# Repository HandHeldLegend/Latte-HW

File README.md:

# Latte Project
This is the official Github page for project Latte from Hand Held Legend.

## Software and PCB License
<br />This firmware and PCB model are licensed under a <a rel="license" href="http://creativecommons.org/licenses/by-nc-sa/3.0/">Creative Commons Attribution-NonCommercial-ShareAlike 3.0 Unported License</a>.

## 3D Models License

<br />The 3D shell, buttons, and other associated models are licensed under a <a rel="license" href="http://creativecommons.org/licenses/by/4.0/">Creative Commons Attribution 4.0 International License</a>.

## Attributions

Resources Cross-Referenced for shell shape:
- 3D Scans by Wesk

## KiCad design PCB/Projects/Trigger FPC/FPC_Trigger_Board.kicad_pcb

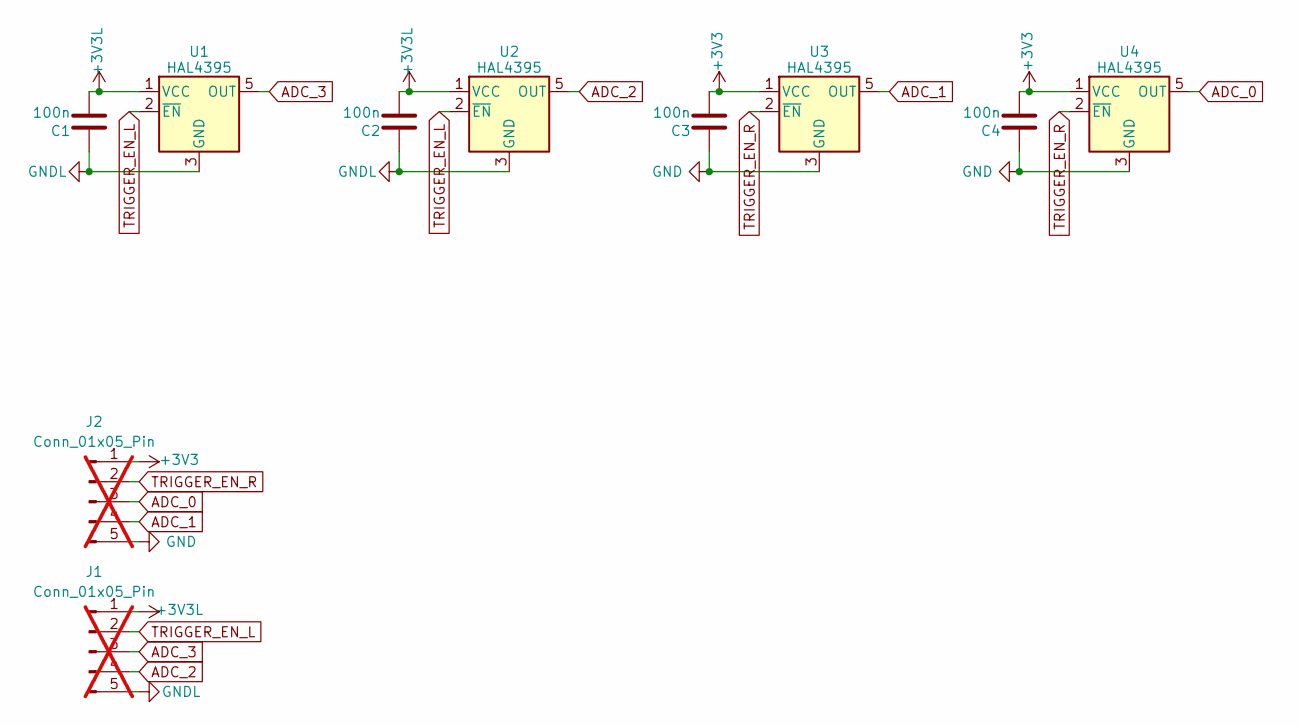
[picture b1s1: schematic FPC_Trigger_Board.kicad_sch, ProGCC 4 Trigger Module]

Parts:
C1, C2, C3, C4: 100n; C_0201_0603Metric; MPN GRM033R61A104KE15D; LCSC C76934
J1, J2: Conn_01x05_Pin; 505110-0592 Ribbon; not fitted
U1, U2, U3, U4: HAL4395; SOT-23-5L; MPN HAL4395SO5; LCSC C49165022

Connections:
+3V3: C3.2, C4.2, J2.1, U3.1 (VCC), U4.1 (VCC)
+3V3L: C1.2, C2.2, J1.1, U1.1 (VCC), U2.1 (VCC)
ADC_0: J2.3, U4.5 (OUT)
ADC_1: J2.4, U3.5 (OUT)
ADC_2: J1.4, U2.5 (OUT)
ADC_3: J1.3, U1.5 (OUT)
GND: C3.1, C4.1, J2.5, U3.3 (GND), U4.3 (GND)
GNDL: C1.1, C2.1, J1.5, U1.3 (GND), U2.3 (GND)
TRIGGER_EN_L: J1.2, U1.2 (~EN), U2.2 (~EN)
TRIGGER_EN_R: J2.2, U3.2 (~EN), U4.2 (~EN)

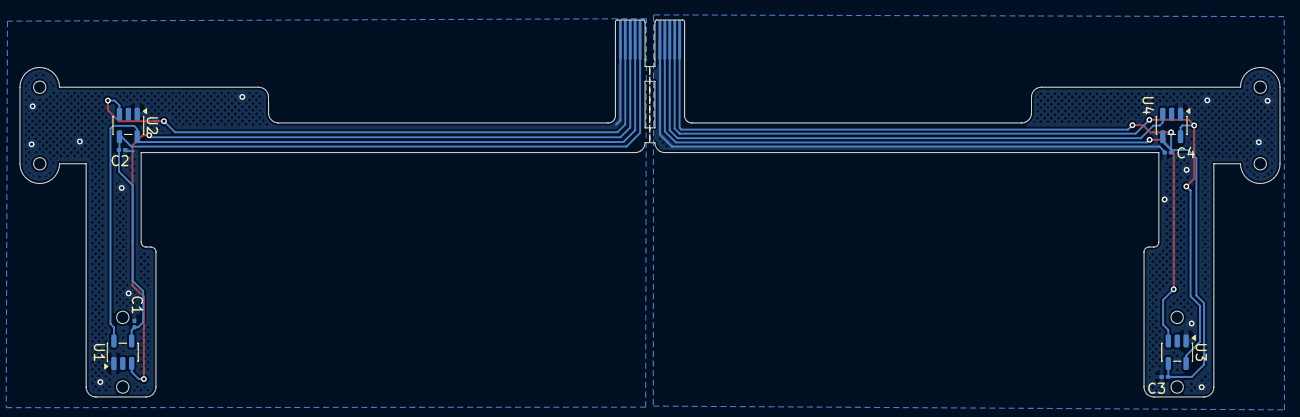
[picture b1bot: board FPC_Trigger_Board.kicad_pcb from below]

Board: 2 copper layers, 127.6 x 38.2 mm, 10 parts (8 on the bottom side), 10 nets.

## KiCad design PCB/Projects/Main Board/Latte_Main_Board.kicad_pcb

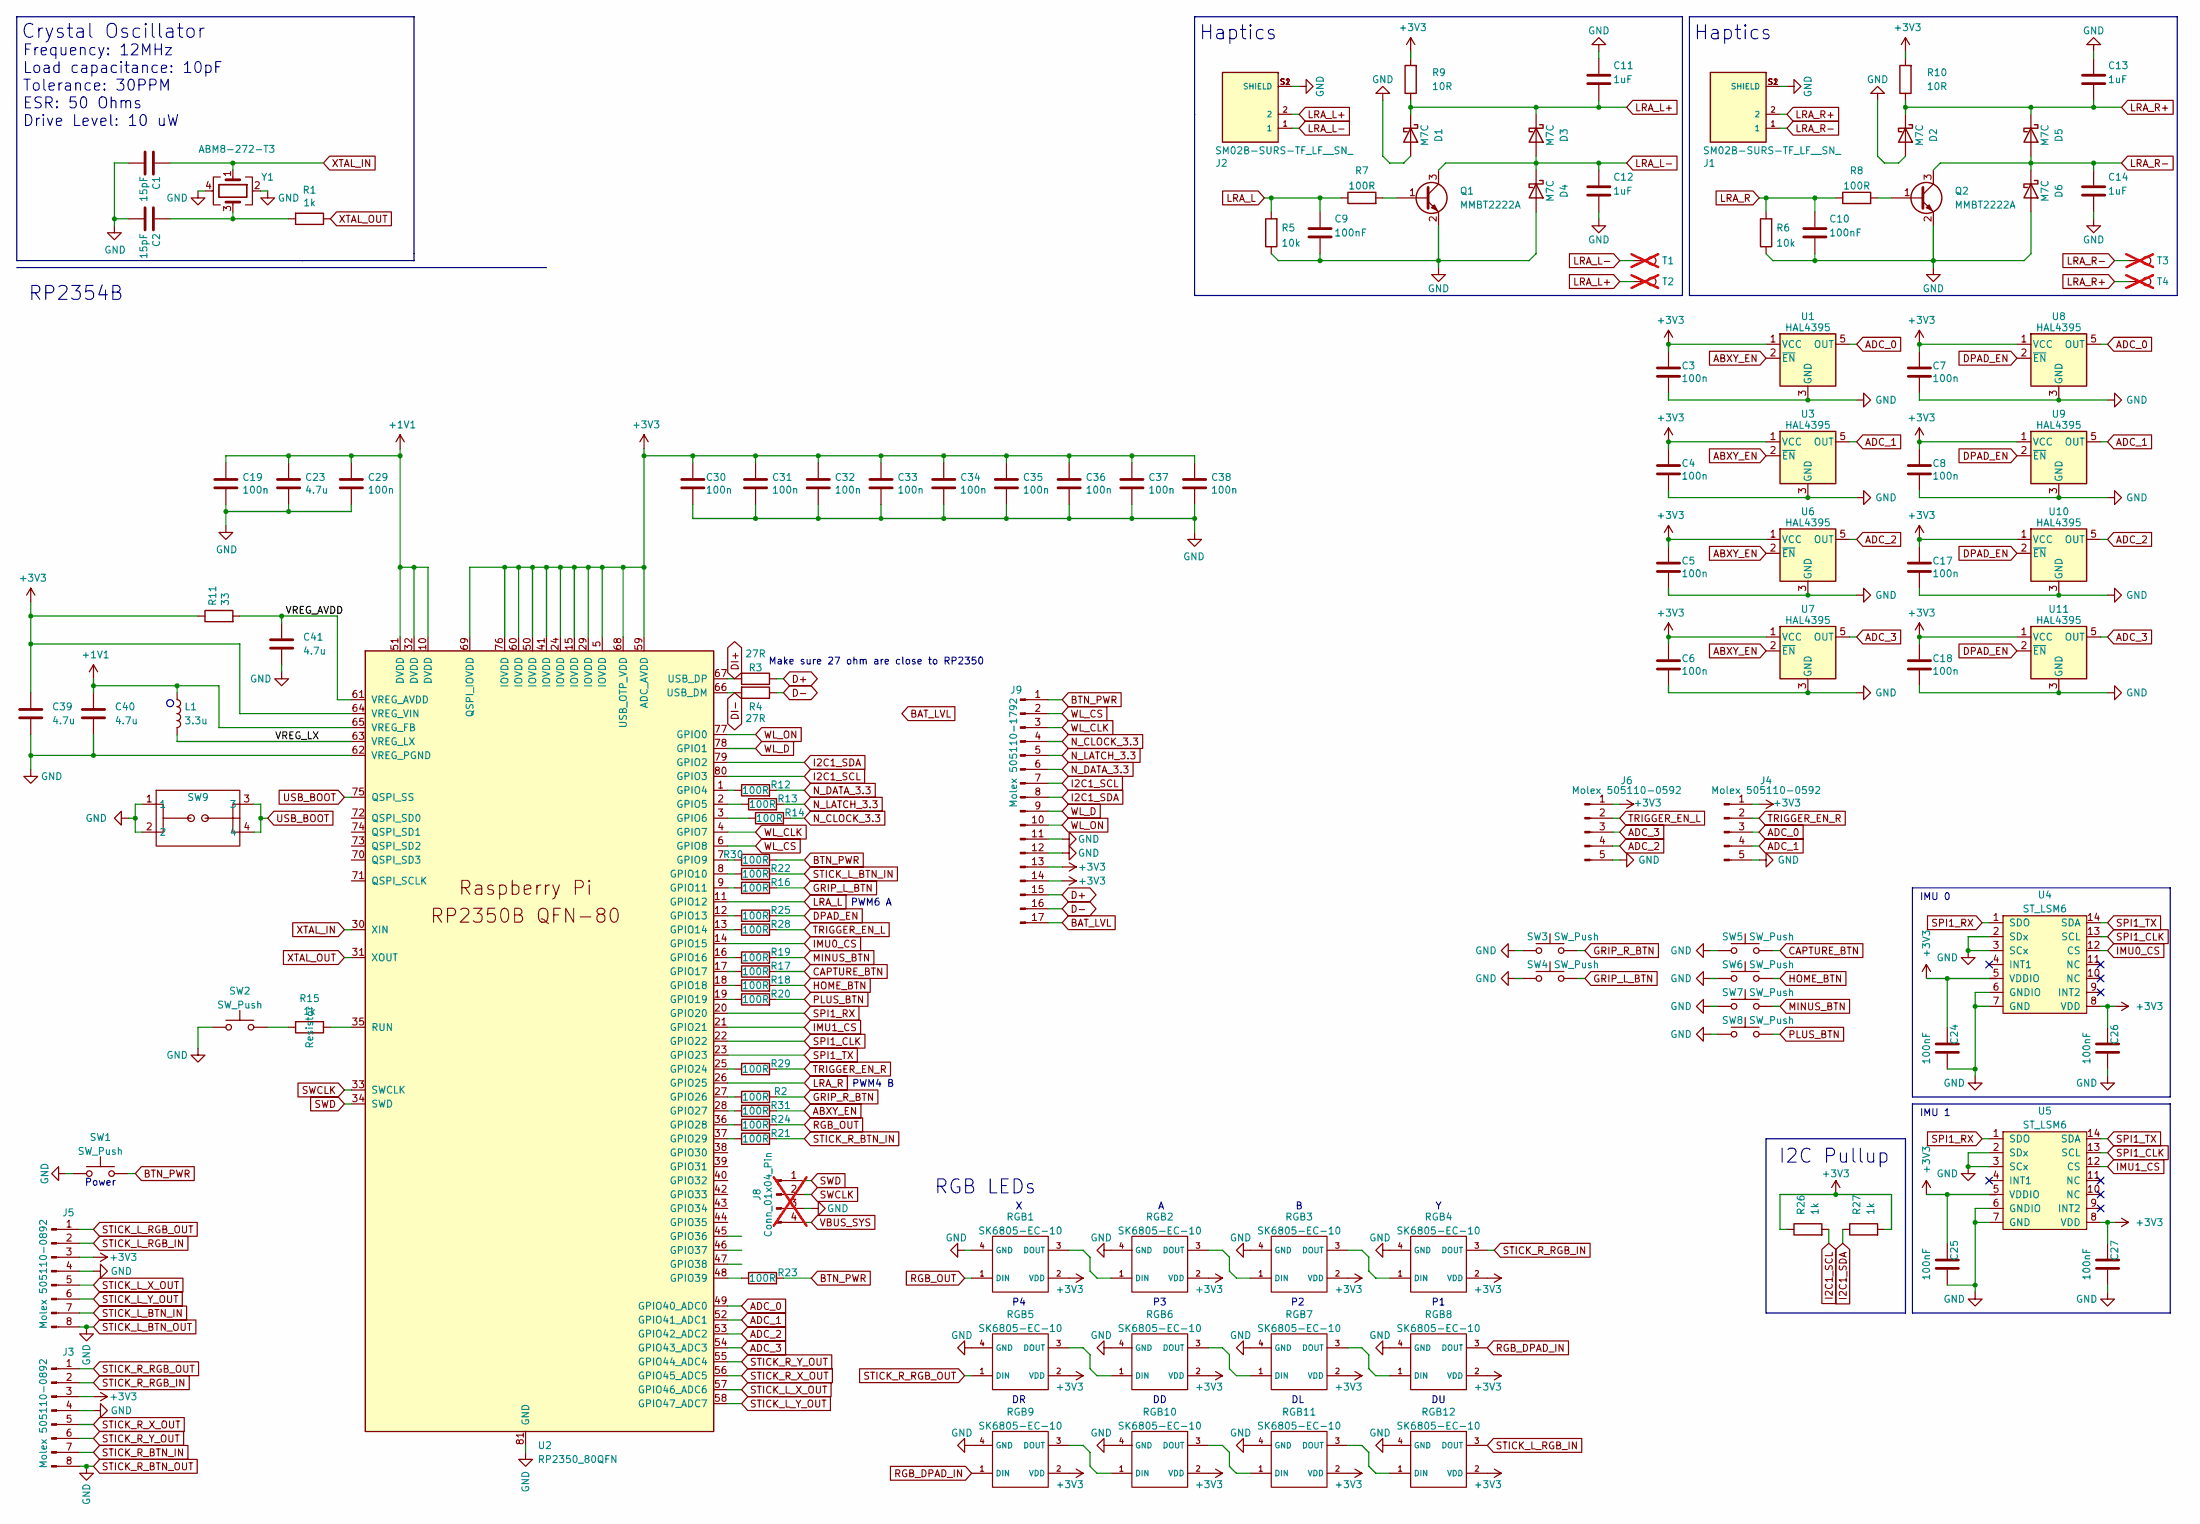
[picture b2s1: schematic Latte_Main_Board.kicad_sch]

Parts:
C1, C2: 15pF; C_0402_1005Metric; MPN CC0402FRNPO9BN150; LCSC C326803
C3, C4, C5, C6, C7, C8, C17, C18, C19, C29, C30, C31, C32, C33, C34, C35, C36, C37, C38: 100n; C_0201_0603Metric; MPN GRM033R61A104KE15D; LCSC C76934
C9, C10, C24, C25, C26, C27: 100nF; C_0201_0603Metric; MPN CL03A104KQ3NNNC; LCSC C160831
C11, C12, C13, C14: 1uF; C_0201_0603Metric; MPN GRM033R60J105KEA2D; LCSC C76929
C23, C39, C40, C41: 4.7u; C_0402_1005Metric; MPN CL05A475KP5NRNC; LCSC C368809
D1, D2, D3, D4, D5, D6: M7C; D_SOD-523; MPN B5819WT; LCSC C5364321
J1, J2: SM02B-SURS-TF_LF__SN_; JST_SM02B-SURS-TF_LF__SN_; PARTREV N/A; LCSC C566239
J3, J5: Molex 505110-0892; 5051100892; MPN 505110-0892; LCSC C5902847
J4, J6: Molex 505110-0592; 5051100592; MPN 505110-0592; LCSC C3168457
J8: Conn_01x04_Pin; PinHeader_1x04_P2.00mm_Vertical; not fitted
J9: Molex 505110-1792; 5051101792; MPN 505110-1792; LCSC C6819458
L1: 3.3u; L_pol_2016; MPN AOTA-B201610S3R3-101-T; LCSC C42411119
Q1, Q2: MMBT2222A; SOT-23; MPN MMBT2222A; LCSC C916372
R1, R15, R26, R27: 1k; R_0201_0603Metric; MPN RC0201FR-071KL; LCSC C138165
R2, R7, R8, R12, R13, R14, R16, R17, R18, R19, R20, R21, R22, R23, R24, R25, R28, R29, R30, R31: 100R; R_0201_0603Metric; MPN RC0201FR-07100RL; LCSC C77623
R3, R4: 27R; R_0201_0603Metric; MPN RC0201FR-0727RL; LCSC C273268
R5, R6: 10k; R_0201_0603Metric; MPN RC0201FR-0710KL; LCSC C106225
R9, R10: 10R; R_0201_0603Metric; MPN RC0201FR-0710RL; LCSC C106226
R11: 33; R_0201_0603Metric; MPN RC0201FR-0733RL; LCSC C295794
RGB1, RGB2, RGB3, RGB4, RGB5, RGB6, RGB7, RGB8, RGB9, RGB10, RGB11, RGB12: SK6805-EC-10; MPN SK6805-EC-10; LCSC C22394946
SW1, SW2, SW3, SW4, SW5, SW6, SW7, SW8: SW_Push; KSC-TE; MPN KSC201J LFS; LCSC C221725
SW9: 1TS026A-1000-0550; MPN 1TS026A-1000-0550; LCSC C913778
T1, T2, T3, T4: PinHeader_1x01_P1.00mm_Vertical; not fitted
U1, U3, U6, U7, U8, U9, U10, U11: HAL4395; SOT-23-5L; MPN HAL4395SO5; LCSC C49165022
U2: RP2350_80QFN; RP2350-QFN-80-1EP_10x10_P0.4mm_EP3.4x3.4mm_ThermalVias; MPN RP2354B; LCSC C39843328
U4, U5: ST_LSM6; LGA14; MPN LSM6DSLTR; LCSC C126672
Y1: ABM8-272-T3; Crystal_SMD_3225-4Pin_3.2x2.5mm; MPN ABM8-272-T3; LCSC C20625731

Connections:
+1V1: C19.1, C23.1, C29.1, C40.1, L1.1, U2.10 (DVDD), U2.32 (DVDD), U2.51 (DVDD), U2.65 (VREG_FB)
+3V3: C3.1, C4.1, C5.1, C6.1, C7.1, C8.1, C17.1, C18.1, C24.2, C25.2, C26.2, C27.2, C30.1, C31.1, C32.1, C33.1, C34.1, C35.1, C36.1, C37.1, C38.1, C39.1, J3.3, J4.1, J5.3, J6.1, J9.13, J9.14, R9.2, R10.2, R11.1, R26.1, R27.2, RGB1.2 (VDD), RGB2.2 (VDD), RGB3.2 (VDD), RGB4.2 (VDD), RGB5.2 (VDD), RGB6.2 (VDD), RGB7.2 (VDD), RGB8.2 (VDD), RGB9.2 (VDD), RGB10.2 (VDD), RGB11.2 (VDD), RGB12.2 (VDD), U1.1 (VCC), U2.5 (IOVDD), U2.15 (IOVDD), U2.24 (IOVDD), U2.29 (IOVDD), U2.41 (IOVDD), U2.50 (IOVDD), U2.59 (ADC_AVDD), U2.60 (IOVDD), U2.64 (VREG_VIN), U2.68 (USB_OTP_VDD), U2.69 (QSPI_IOVDD), U2.76 (IOVDD), U3.1 (VCC), U4.5 (VDDIO), U4.8 (VDD), U5.5 (VDDIO), U5.8 (VDD), U6.1 (VCC), U7.1 (VCC), U8.1 (VCC), U9.1 (VCC), U10.1 (VCC), U11.1 (VCC)
/VREG_AVDD: C41.1, R11.2, U2.61 (VREG_AVDD)
/VREG_LX: L1.2, U2.63 (VREG_LX)
ABXY_EN: R31.2, U1.2 (~EN), U3.2 (~EN), U6.2 (~EN), U7.2 (~EN)
ADC_0: J4.3, U1.5 (OUT), U2.49 (GPIO40_ADC0), U8.5 (OUT)
ADC_1: J4.4, U2.52 (GPIO41_ADC1), U3.5 (OUT), U9.5 (OUT)
ADC_2: J6.4, U2.53 (GPIO42_ADC2), U6.5 (OUT), U10.5 (OUT)
ADC_3: J6.3, U2.54 (GPIO43_ADC3), U7.5 (OUT), U11.5 (OUT)
BAT_LVL: J9.17
BTN_PWR: J9.1, R23.2, R30.2, SW1.2
CAPTURE_BTN: R17.2, SW5.2
D+: J9.15, R3.1
D-: J9.16, R4.1
DI+: R3.2, U2.67 (USB_DP)
DI-: R4.2, U2.66 (USB_DM)
DPAD_EN: R25.2, U8.2 (~EN), U9.2 (~EN), U10.2 (~EN), U11.2 (~EN)
GRIP_L_BTN: R16.2, SW4.2
GRIP_R_BTN: R2.2, SW3.2
HOME_BTN: R18.2, SW6.2
I2C1_SCL: J9.7, R26.2, U2.80 (GPIO3)
I2C1_SDA: J9.8, R27.1, U2.79 (GPIO2)
IMU0_CS: U2.14 (GPIO15), U4.12 (CS)
IMU1_CS: U2.21 (GPIO21), U5.12 (CS)
LRA_L: C9.1, R5.2, R7.1, U2.11 (GPIO12)
LRA_L+: C11.2, D1.1 (K), D3.1 (K), J2.2, R9.1, T2.1
LRA_L-: C12.1, D3.2 (A), D4.1 (K), J2.1, Q1.3 (C), T1.1
LRA_R: C10.1, R6.2, R8.1, U2.26 (GPIO25)
LRA_R+: C13.2, D2.1 (K), D5.1 (K), J1.2, R10.1, T4.1
LRA_R-: C14.1, D5.2 (A), D6.1 (K), J1.1, Q2.3 (C), T3.1
MINUS_BTN: R19.2, SW7.2
N_CLOCK_3.3: J9.4, R14.2
N_DATA_3.3: J9.6, R12.2
N_LATCH_3.3: J9.5, R13.2
unnamed: C2.1, R1.2, Y1.3
unnamed: Q1.1 (B), R7.2
unnamed: Q2.1 (B), R8.2
unnamed: R15.2, SW2.2
unnamed: RGB1.3 (DOUT), RGB2.1 (DIN)
unnamed: RGB2.3 (DOUT), RGB3.1 (DIN)
unnamed: RGB3.3 (DOUT), RGB4.1 (DIN)
unnamed: RGB5.3 (DOUT), RGB6.1 (DIN)
unnamed: RGB6.3 (DOUT), RGB7.1 (DIN)
unnamed: RGB7.3 (DOUT), RGB8.1 (DIN)
unnamed: RGB9.3 (DOUT), RGB10.1 (DIN)
unnamed: RGB10.3 (DOUT), RGB11.1 (DIN)
unnamed: RGB11.3 (DOUT), RGB12.1 (DIN)
unnamed: R12.1, U2.1 (GPIO4)
unnamed: R13.1, U2.2 (GPIO5)
unnamed: R14.1, U2.3 (GPIO6)
unnamed: R30.1, U2.7 (GPIO9)
unnamed: R22.1, U2.8 (GPIO10)
unnamed: R16.1, U2.9 (GPIO11)
unnamed: R25.1, U2.12 (GPIO13)
unnamed: R28.1, U2.13 (GPIO14)
unnamed: R19.1, U2.16 (GPIO16)
unnamed: R17.1, U2.17 (GPIO17)
unnamed: R18.1, U2.18 (GPIO18)
unnamed: R20.1, U2.19 (GPIO19)
unnamed: R29.1, U2.25 (GPIO24)
unnamed: R2.1, U2.27 (GPIO26)
unnamed: R31.1, U2.28 (GPIO27)
unnamed: R24.1, U2.36 (GPIO28)
unnamed: R21.1, U2.37 (GPIO29)
unnamed: R23.1, U2.48 (GPIO39)
unnamed: R15.1, U2.35 (RUN)
PLUS_BTN: R20.2, SW8.2
RGB_DPAD_IN: RGB8.3 (DOUT), RGB9.1 (DIN)
RGB_OUT: R24.2, RGB1.1 (DIN)
SPI1_CLK: U2.22 (GPIO22), U4.13 (SCL), U5.13 (SCL)
SPI1_RX: U2.20 (GPIO20), U4.1 (SDO), U5.1 (SDO)
SPI1_TX: U2.23 (GPIO23), U4.14 (SDA), U5.14 (SDA)
STICK_L_BTN_IN: J5.7, R22.2
STICK_L_BTN_OUT: C1.2, C2.2, C3.2, C4.2, C5.2, C6.2, C7.2, C8.2, C9.2, C10.2, C11.1, C12.2, C13.1, C14.2, C17.2, C18.2, C19.2, C23.2, C24.1, C25.1, C26.1, C27.1, C29.2, C30.2, C31.2, C32.2, C33.2, C34.2, C35.2, C36.2, C37.2, C38.2, C39.2, C40.2, C41.2, D1.2 (A), D2.2 (A), D4.2 (A), D6.2 (A), J1.S1 (SHIELD), J1.S2 (SHIELD), J2.S1 (SHIELD), J2.S2 (SHIELD), J3.4, J3.8, J4.5, J5.4, J5.8, J6.5, J8.3, J9.11, J9.12, Q1.2 (E), Q2.2 (E), R5.1, R6.1, RGB1.4 (GND), RGB2.4 (GND), RGB3.4 (GND), RGB4.4 (GND), RGB5.4 (GND), RGB6.4 (GND), RGB7.4 (GND), RGB8.4 (GND), RGB9.4 (GND), RGB10.4 (GND), RGB11.4 (GND), RGB12.4 (GND), SW1.1, SW2.1, SW3.1, SW4.1, SW5.1, SW6.1, SW7.1, SW8.1, SW9.1, SW9.2, U1.3 (GND), U2.62 (VREG_PGND), U2.81 (GND), U3.3 (GND), U4.2 (SDx), U4.3 (SCx), U4.6 (GNDIO), U4.7 (GND), U5.2 (SDx), U5.3 (SCx), U5.6 (GNDIO), U5.7 (GND), U6.3 (GND), U7.3 (GND), U8.3 (GND), U9.3 (GND), U10.3 (GND), U11.3 (GND), Y1.2, Y1.4
STICK_L_RGB_IN: J5.2, RGB12.3 (DOUT)
STICK_L_RGB_OUT: J5.1
STICK_L_X_OUT: J5.5, U2.57 (GPIO46_ADC6)
STICK_L_Y_OUT: J5.6, U2.58 (GPIO47_ADC7)
STICK_R_BTN_IN: J3.7, R21.2
STICK_R_RGB_IN: J3.2, RGB4.3 (DOUT)
STICK_R_RGB_OUT: J3.1, RGB5.1 (DIN)
STICK_R_X_OUT: J3.5, U2.56 (GPIO45_ADC5)
STICK_R_Y_OUT: J3.6, U2.55 (GPIO44_ADC4)
SWCLK: J8.2, U2.33 (SWCLK)
SWD: J8.1, U2.34 (SWD)
TRIGGER_EN_L: J6.2, R28.2
TRIGGER_EN_R: J4.2, R29.2
USB_BOOT: SW9.3, SW9.4, U2.75 (QSPI_SS)
VBUS_SYS: J8.4
WL_CLK: J9.3, U2.4 (GPIO7)
WL_CS: J9.2, U2.6 (GPIO8)
WL_D: J9.9, U2.78 (GPIO1)
WL_ON: J9.10, U2.77 (GPIO0)
XTAL_IN: C1.1, U2.30 (XIN), Y1.1
XTAL_OUT: R1.1, U2.31 (XOUT)

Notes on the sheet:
Power
PWM6 A
RP2354B
Haptics
RGB LEDs
Crystal Oscillator
IMU 1
PWM4 B
IMU 0
I2C Pullup
Frequency: 12MHz Load capacitance: 10pF Tolerance: 30PPM ESR: 50 Ohms Drive Level: 10 uW
Make sure 27 ohm are close to RP2350

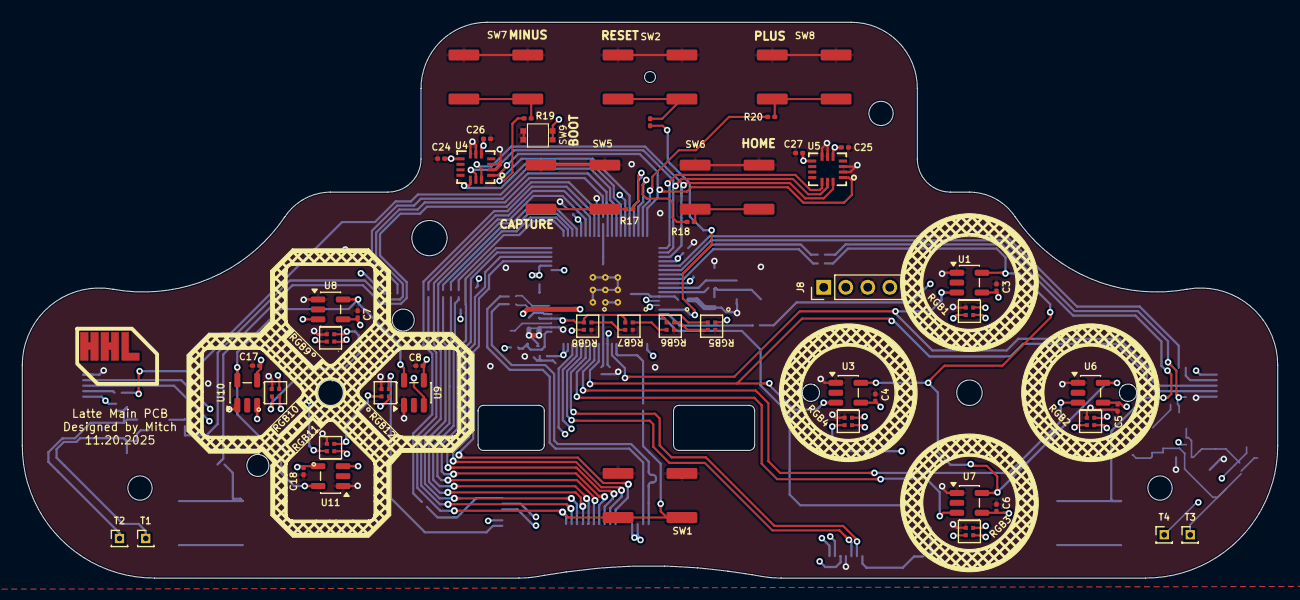
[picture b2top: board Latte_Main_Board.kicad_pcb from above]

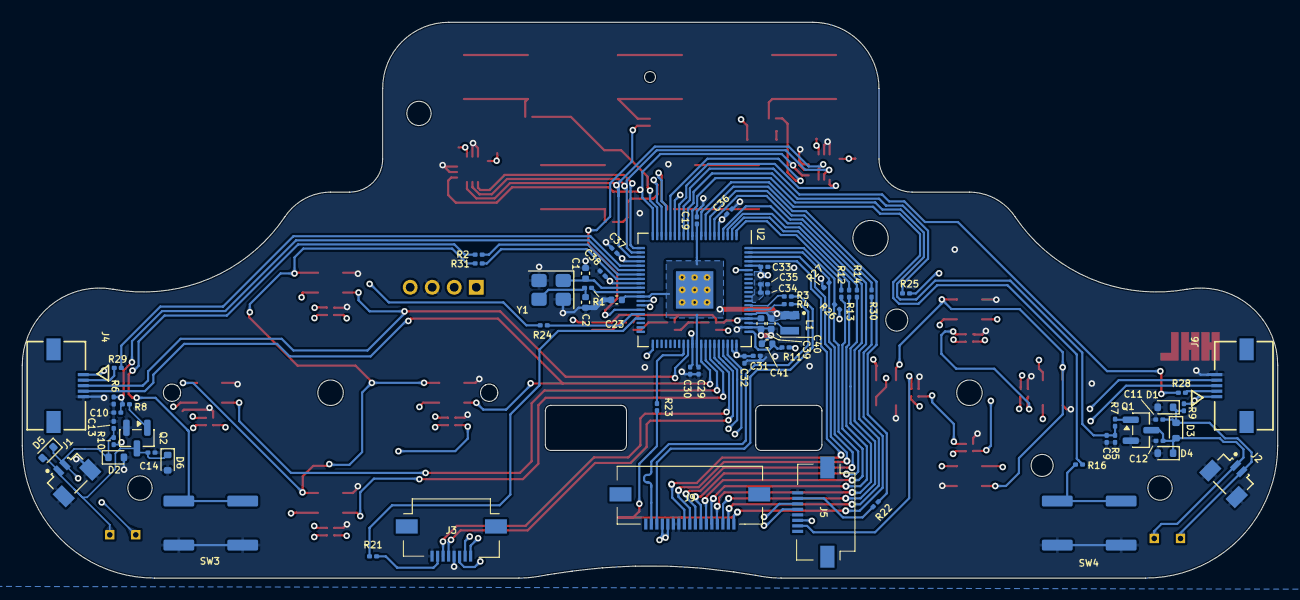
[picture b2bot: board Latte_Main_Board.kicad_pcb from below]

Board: 4 copper layers, 114.0 x 50.5 mm, 120 parts (69 on the bottom side), 92 nets.

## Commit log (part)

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2025-10-30 Initialize README with project information
    Added project details, licenses, and attributions to README.
2025-10-30 Routing updates
2025-11-02 fun outline
2025-11-04 Prod 1
2025-11-12 3D Files Initial STLs
2025-11-12 Fix joystick internal shaft diameter
2025-11-18 STL Updates
    - DPAD and SEWN buttons are modified to have adhesive recesses
    - RSUPPORT and LSUPPORT offset to get out of the way of solder joints
    - TOPSHELL is updated to feature glyphs for menu buttons
    - GRIPBUTTONR and GRIPBUTTONL have a 15 degree shift for one of the alignment nubs to assist with installation ease. Ensures they only fit on one side.
    - LOWERSHELL has been updated to match the changes for the GRIPBUTTON changes
    - LOWERMENU and UPPERMENU have been changed to just be MENU
2025-11-19 PCB Update
    - Missing BOOT switch added
2025-11-20 Silkscreen updates
2025-11-20 PCB Updates
2025-11-20 Printables
2025-12-12 FPC Fixes
2025-12-12 3d Updates
2026-01-03 FPC Board Update
